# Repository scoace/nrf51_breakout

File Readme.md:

nrf51822 YJ-14015 Breakout Board

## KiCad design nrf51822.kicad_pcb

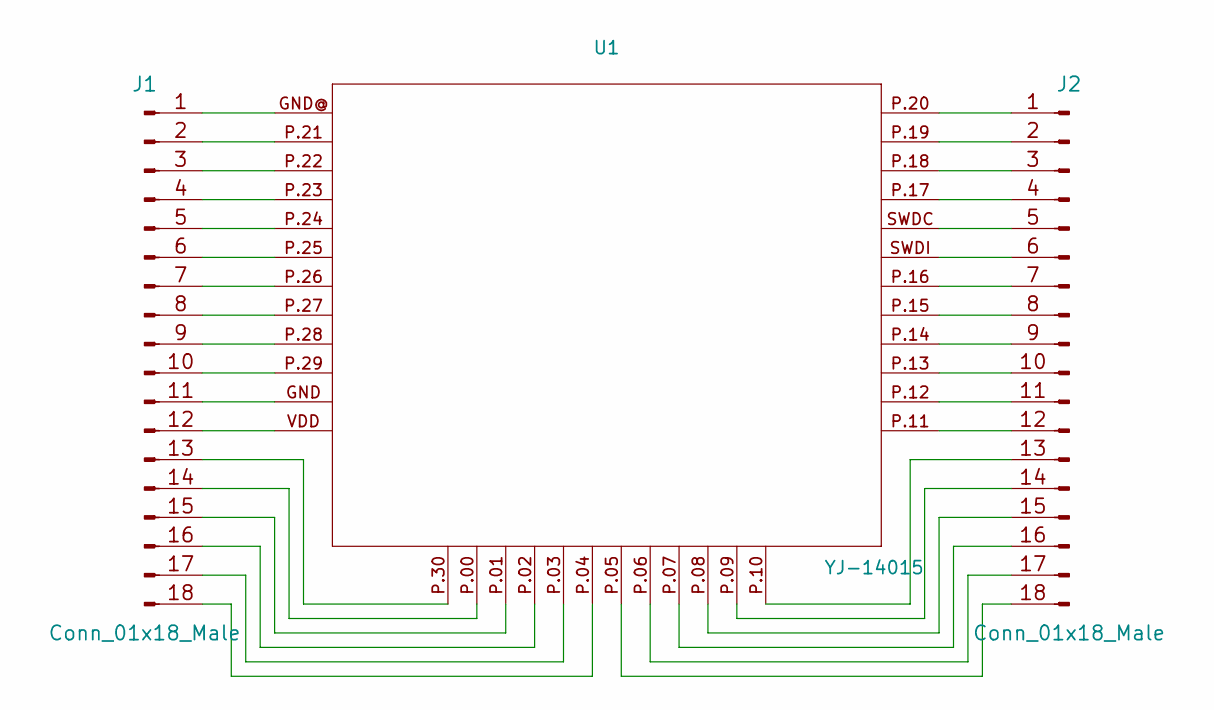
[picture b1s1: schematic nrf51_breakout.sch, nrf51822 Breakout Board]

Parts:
J1, J2: Conn_01x18_Male; Pin_Header_Straight_1x18_Pitch2.54mm
U1: YJ-14015; YJ-14015-Modul

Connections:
unnamed: J1.1, U1.GND@ (GND)
unnamed: J1.2, U1.P.21 (P0.21)
unnamed: J1.3, U1.P.22 (P0.22)
unnamed: J1.4, U1.P.23 (P0.23)
unnamed: J1.5, U1.P.24 (P0.24)
unnamed: J1.6, U1.P.25 (P0.25)
unnamed: J1.7, U1.P.26 (P0.26)
unnamed: J1.8, U1.P.27 (P0.27)
unnamed: J1.9, U1.P.28 (P0.28)
unnamed: J1.10, U1.P.29 (P0.29)
unnamed: J1.11, U1.GND
unnamed: J1.12, U1.VDD
unnamed: J1.13, U1.P.30 (P0.30)
unnamed: J1.14, U1.P.00 (P0.00)
unnamed: J1.15, U1.P.01 (P0.01)
unnamed: J1.16, U1.P.02 (P0.02)
unnamed: J1.17, U1.P.03 (P0.03)
unnamed: J1.18, U1.P.04 (P0.04)
unnamed: J2.1, U1.P.20 (P0.20)
unnamed: J2.2, U1.P.19 (P0.19)
unnamed: J2.3, U1.P.18 (P0.18)
unnamed: J2.4, U1.P.17 (P0.17)
unnamed: J2.5, U1.SWDC (SWDCLK)
unnamed: J2.6, U1.SWDI (SWDIO/NRESET)
unnamed: J2.7, U1.P.16 (P0.16)
unnamed: J2.8, U1.P.15 (P0.15)
unnamed: J2.9, U1.P.14 (P0.14)
unnamed: J2.10, U1.P.13 (P0.13)
unnamed: J2.11, U1.P.12 (P0.12)
unnamed: J2.12, U1.P.11 (P0.11)
unnamed: J2.13, U1.P.10 (P0.10)
unnamed: J2.14, U1.P.09 (P0.09)
unnamed: J2.15, U1.P.08 (P0.08)
unnamed: J2.16, U1.P.07 (P0.07)
unnamed: J2.17, U1.P.06 (P0.06)
unnamed: J2.18, U1.P.05 (P0.05)

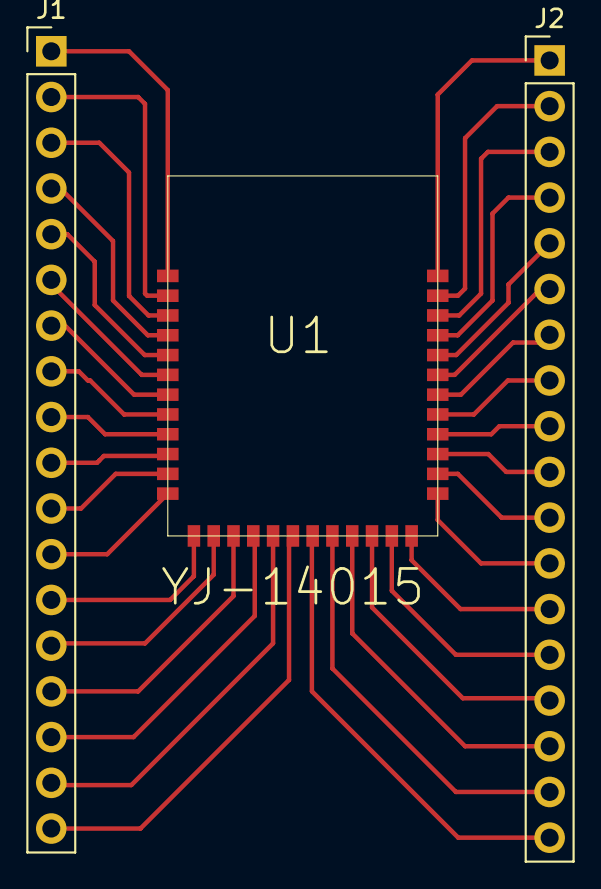
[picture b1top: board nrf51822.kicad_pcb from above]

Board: 2 copper layers, 3 parts (0 on the bottom side), 36 nets.

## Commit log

2018-03-24 Second Commit
2018-03-24 Third Commit
2018-03-24 Fourth Commit
